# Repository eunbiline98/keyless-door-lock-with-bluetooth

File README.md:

# keyless-door-lock-with-bluetooth

This project consists of a smart door lock system. In this case we have developed a great solution to improve the Door lock system. how to operate this door lock is very easy. just bring the Bluetooth keyless that has been registered with the Mac Address into the Microcontroller, then connect the relay to be used to operate the active and inactive contacts of the magnetic door lock, because the magnetic door lock system will be active if it is given a 220V AC voltage. In this method, all data is controlled by Bluetooth keyless, ESP32 is used as Controller, we know that ESP32 has built-in Bluetooth and Wi-fi support.

# Hardware

- ESP32
- Relay Module 1CH
- Hi-Link 5V
- Door Magnetic 220VAC

# Diagram Wiring

# Board
## Schematic

## Layout
### Top

### Bottom

### 3D Pov-ray

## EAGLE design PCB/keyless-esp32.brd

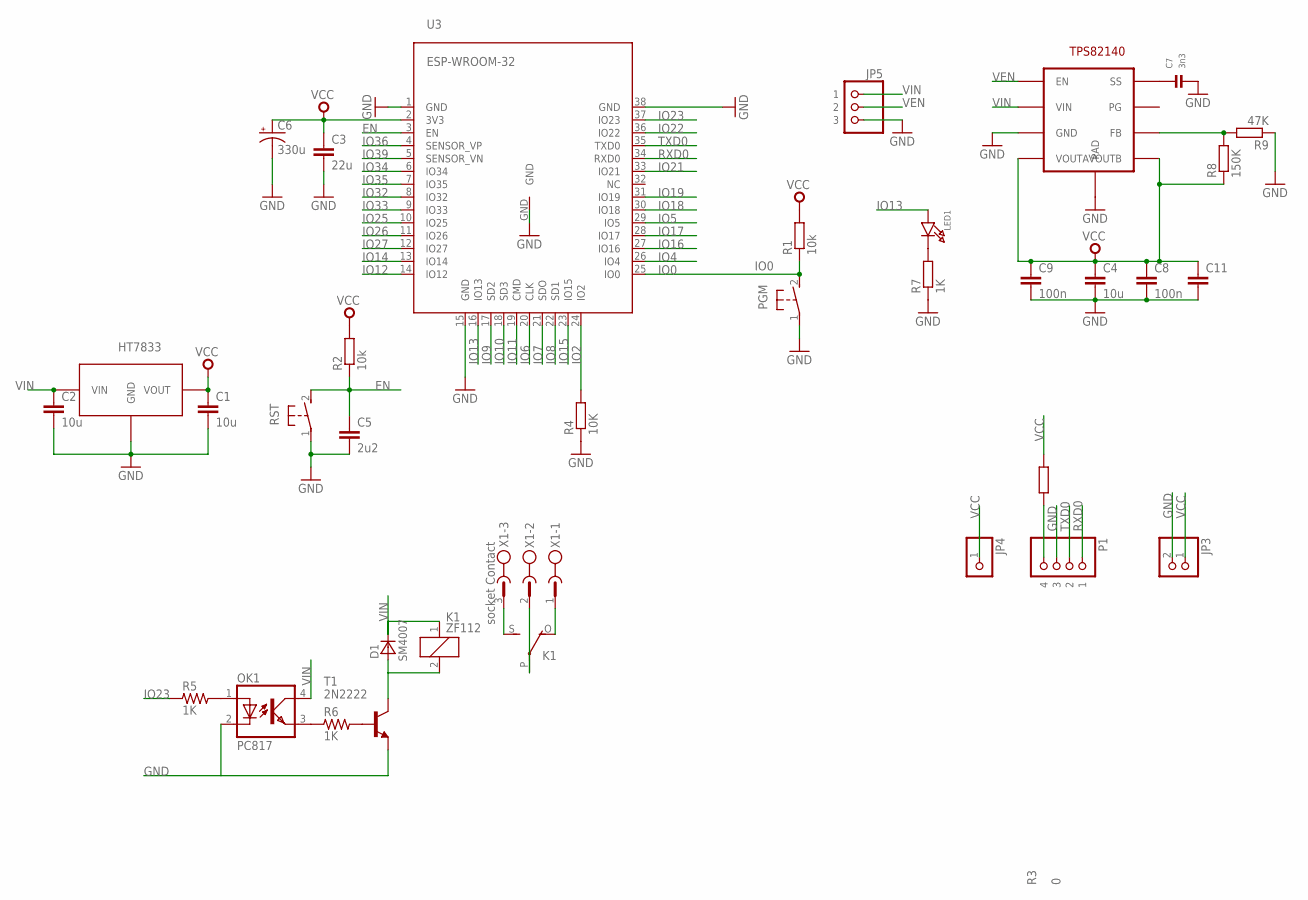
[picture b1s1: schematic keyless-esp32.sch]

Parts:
C1, C2, C4: 10u; C0603
C3: 22u; 0805
C5: 2u2; C0603
C6: 330u; VISHAY_C
C7: 3n3; 0603
C8, C9: 100n; C0603
C11: CAPSMD; GRM43D
D1: SM4007; MELF-MLL41
JP3: HEADER-1X2ROUND; 1X02_ROUND
JP4: HEADER-1X1ROUND; 1X01_ROUND
JP5: HEADER-1X3ROUND; 1X03_ROUND
K1: ZF112
LED1: LED0603; CHIPLED_0603
OK1: PC817; DIL04
P1: HEADER-1X4ROUND; 1X04_ROUND
PGM: DTSM-3
R1, R2: 10k; R0603
R3: 0; R0603
R4: 10K; R0603
R5, R6: 1K; R0805
R7: 1K; R0603
R8: 150K; R0603
R9: 47K; R0603
RST: DTSM-3
T1: 2N2222; TO18
U3: ESP-WROOM-32
U$1: HT7833; SOT89
U$2: TPS82140
X1: socket Contact; W232-3

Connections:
EN: C5.1, R2.1, RST.2, U3.3 (EN)
GND: C1.2, C2.2, C3.2, C4.2, C5.2, C6.-, C7.2, C8.2, C9.2, C11.C (2), JP3.2, JP5.3, OK1.2 (C), P1.3, PGM.1, R4.1, R7.1, R9.1, RST.1, T1.1 (E), U3.1 (GND), U3.15 (GND), U3.38 (GND), U3.GND, U$1.GND, U$2.P$3 (GND), U$2.P$9 (PAD)
IO0: PGM.2, R1.1, U3.25 (IO0)
IO2: R4.2, U3.24 (IO2)
IO4: U3.26 (IO4)
IO5: U3.29 (IO5)
IO6: U3.20 (CLK)
IO7: U3.21 (SDO)
IO8: U3.22 (SD1)
IO9: U3.17 (SD2)
IO10: U3.18 (SD3)
IO11: U3.19 (CMD)
IO12: U3.14 (IO12)
IO13: LED1.A, U3.16 (IO13)
IO14: U3.13 (IO14)
IO15: U3.23 (IO15)
IO16: U3.27 (IO16)
IO17: U3.28 (IO17)
IO18: U3.30 (IO18)
IO19: U3.31 (IO19)
IO21: U3.33 (IO21)
IO22: U3.36 (IO22)
IO23: R5.1, U3.37 (IO23)
IO25: U3.10 (IO25)
IO26: U3.11 (IO26)
IO27: U3.12 (IO27)
IO32: U3.8 (IO32)
IO33: U3.9 (IO33)
IO34: U3.6 (IO34)
IO35: U3.7 (IO35)
IO36: U3.4 (SENSOR_VP)
IO39: U3.5 (SENSOR_VN)
unnamed: P1.4, R3.1
unnamed: LED1.C, R7.2
unnamed: C7.1, U$2.P$8 (SS)
unnamed: R8.2, R9.2, U$2.P$6 (FB)
unnamed: R6.2, T1.2 (B)
unnamed: OK1.3 (EMIT), R6.1
unnamed: OK1.1 (A), R5.2
unnamed: K1.O, X1.1
unnamed: K1.P, X1.2
unnamed: D1.A, K1.2, T1.3 (C)
unnamed: K1.S, X1.3
RXD0: P1.1, U3.34 (RXD0)
TXD0: P1.2, U3.35 (TXD0)
VCC: C1.1, C3.1, C4.1, C6.+, C8.1, C9.1, C11.A (1), JP3.1, JP4.1, R1.2, R2.2, R3.2, R8.1, U3.2 (3V3), U$1.VOUT, U$2.P$4 (VOUTA), U$2.P$5 (VOUTB)
VEN: JP5.2, U$2.P$1 (EN)
VIN: C2.1, D1.C, JP5.1, K1.1, OK1.4 (COL), U$1.VIN, U$2.P$2 (VIN)

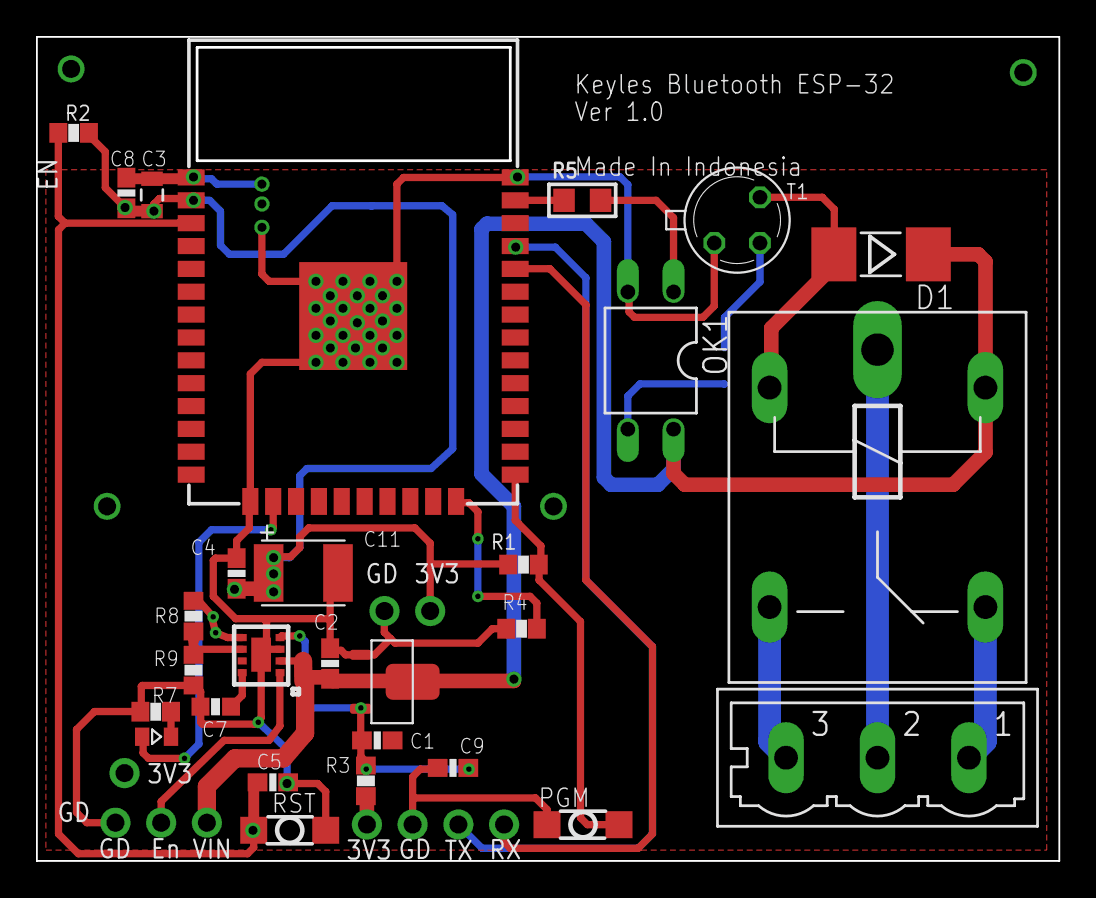
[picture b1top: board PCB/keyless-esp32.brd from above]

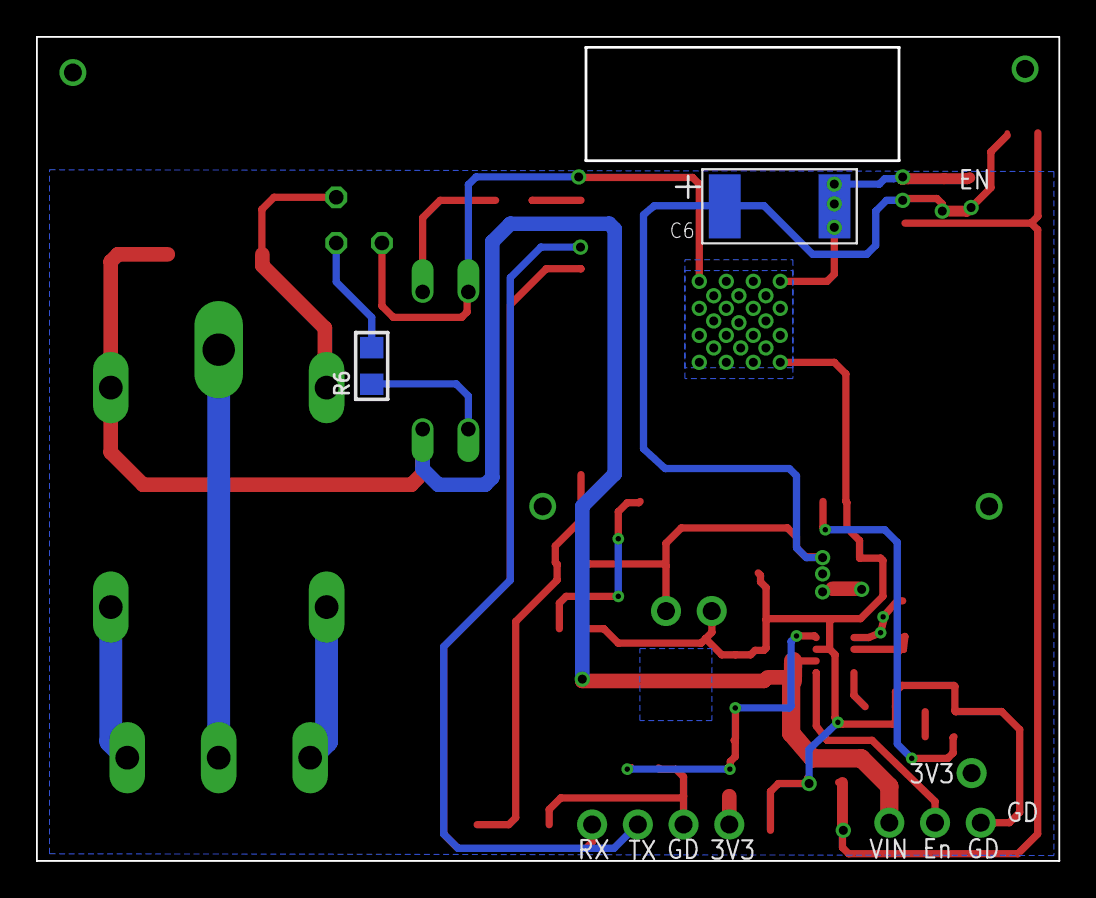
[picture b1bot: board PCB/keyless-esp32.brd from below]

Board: 2 copper layers, 56.7 x 45.7 mm, 34 parts (2 on the bottom side), 22 nets.

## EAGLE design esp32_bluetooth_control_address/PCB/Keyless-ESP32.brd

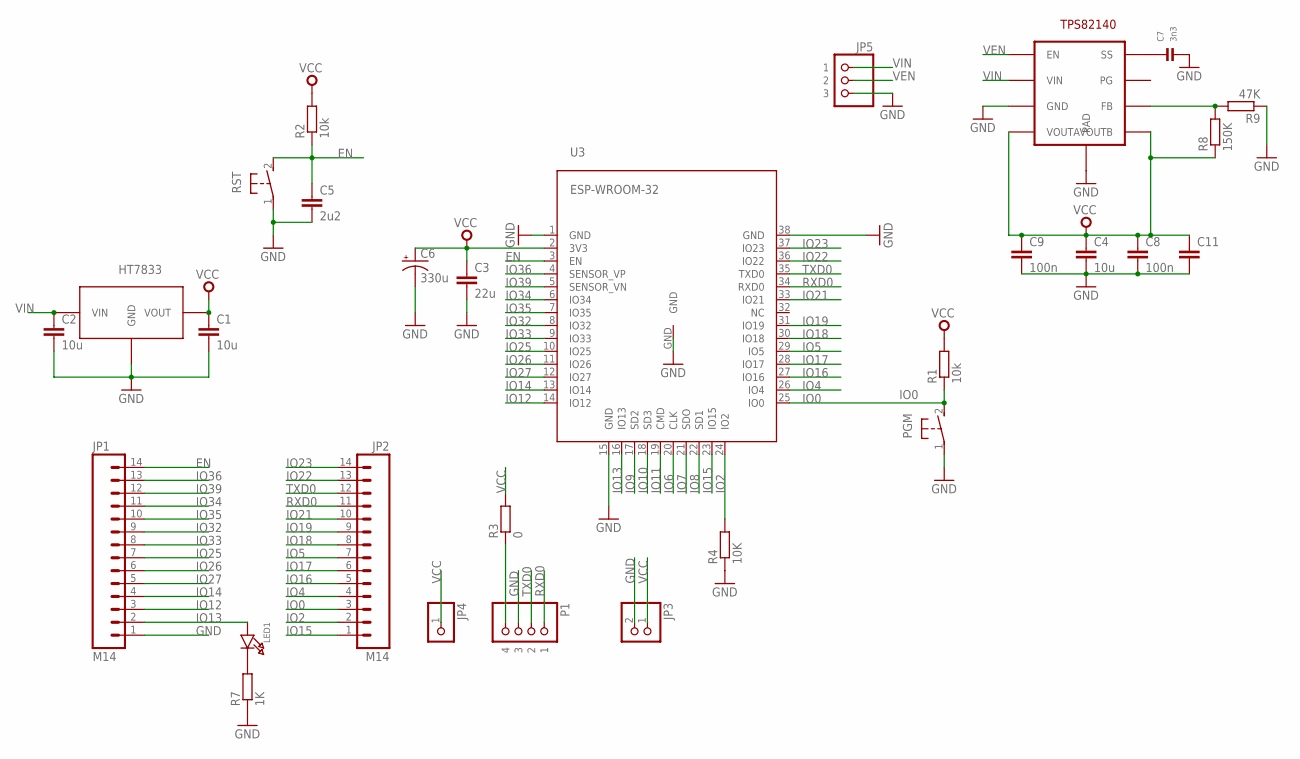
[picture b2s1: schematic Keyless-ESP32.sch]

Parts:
C1, C2, C4: 10u; C0603
C3: 22u; 0805
C5: 2u2; C0603
C6: 330u; VISHAY_C
C7: 3n3; 0603
C8, C9: 100n; C0603
C11: CAPSMD; GRM43D
JP1, JP2: M14; 1X14
JP3: HEADER-1X2ROUND; 1X02_ROUND
JP4: HEADER-1X1ROUND; 1X01_ROUND
JP5: HEADER-1X3ROUND; 1X03_ROUND
LED1: LED0603; CHIPLED_0603
P1: HEADER-1X4ROUND; 1X04_ROUND
PGM: DTSM-3
R1, R2: 10k; R0603
R3: 0; R0603
R4: 10K; R0603
R7: 1K; R0603
R8: 150K; R0603
R9: 47K; R0603
RST: DTSM-3
U3: ESP-WROOM-32
U$1: HT7833; SOT89
U$2: TPS82140

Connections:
EN: C5.1, JP1.14, R2.1, RST.2, U3.3 (EN)
GND: C1.2, C2.2, C3.2, C4.2, C5.2, C6.-, C7.2, C8.2, C9.2, C11.C (2), JP1.1, JP3.2, JP5.3, P1.3, PGM.1, R4.1, R7.1, R9.1, RST.1, U3.1 (GND), U3.15 (GND), U3.38 (GND), U3.GND, U$1.GND, U$2.P$3 (GND), U$2.P$9 (PAD)
IO0: JP2.3, PGM.2, R1.1, U3.25 (IO0)
IO2: JP2.2, R4.2, U3.24 (IO2)
IO4: JP2.4, U3.26 (IO4)
IO5: JP2.7, U3.29 (IO5)
IO6: U3.20 (CLK)
IO7: U3.21 (SDO)
IO8: U3.22 (SD1)
IO9: U3.17 (SD2)
IO10: U3.18 (SD3)
IO11: U3.19 (CMD)
IO12: JP1.3, U3.14 (IO12)
IO13: JP1.2, LED1.A, U3.16 (IO13)
IO14: JP1.4, U3.13 (IO14)
IO15: JP2.1, U3.23 (IO15)
IO16: JP2.5, U3.27 (IO16)
IO17: JP2.6, U3.28 (IO17)
IO18: JP2.8, U3.30 (IO18)
IO19: JP2.9, U3.31 (IO19)
IO21: JP2.10, U3.33 (IO21)
IO22: JP2.13, U3.36 (IO22)
IO23: JP2.14, U3.37 (IO23)
IO25: JP1.7, U3.10 (IO25)
IO26: JP1.6, U3.11 (IO26)
IO27: JP1.5, U3.12 (IO27)
IO32: JP1.9, U3.8 (IO32)
IO33: JP1.8, U3.9 (IO33)
IO34: JP1.11, U3.6 (IO34)
IO35: JP1.10, U3.7 (IO35)
IO36: JP1.13, U3.4 (SENSOR_VP)
IO39: JP1.12, U3.5 (SENSOR_VN)
unnamed: P1.4, R3.1
unnamed: LED1.C, R7.2
unnamed: C7.1, U$2.P$8 (SS)
unnamed: R8.2, R9.2, U$2.P$6 (FB)
RXD0: JP2.11, P1.1, U3.34 (RXD0)
TXD0: JP2.12, P1.2, U3.35 (TXD0)
VCC: C1.1, C3.1, C4.1, C6.+, C8.1, C9.1, C11.A (1), JP3.1, JP4.1, R1.2, R2.2, R3.2, R8.1, U3.2 (3V3), U$1.VOUT, U$2.P$4 (VOUTA), U$2.P$5 (VOUTB)
VEN: JP5.2, U$2.P$1 (EN)
VIN: C2.1, JP5.1, U$1.VIN, U$2.P$2 (VIN)

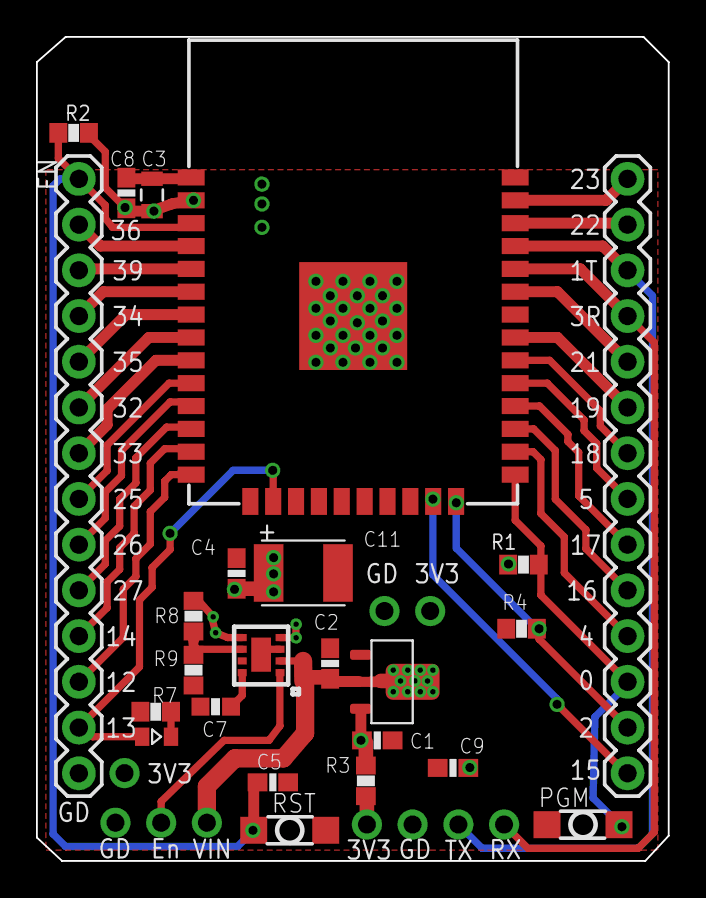
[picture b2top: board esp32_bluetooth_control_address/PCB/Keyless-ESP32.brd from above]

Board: 2 copper layers, 35.1 x 45.8 mm, 29 parts (1 on the bottom side), 35 nets.

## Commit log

2021-08-22 Upload Program ESP_32 (ArduinoIDE 1.8.12)
2022-03-06 Intial Commit
2022-03-06 Adding PCB design
2022-03-06 Adding file pov-ray

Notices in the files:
parts and their libraries:
SparkFun-Passives: Licensing: Creative Commons ShareAlike 4.0 International - https://creativecommons.org/licenses/by-sa/4.0
rc-master-smd: Copyright (C) 2007, Bob Starr
